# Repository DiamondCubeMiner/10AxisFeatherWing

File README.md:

# 10AxisFeatherWing #
A 10-DOF Featherwing, powered by BNO055 and BME280.

## Description ##
This featherwing uses I2C to connect both the IMU (BNO055) and the altimeter (BME280) to the Feather.
I made this to design projects that require a 10-DOF IMU in a tiny package where breakouts can affect the weight a lot and may not be a good option, such as a quadcopter, a model plane, or a model rocket.

## Drivers ##
This project is designed to use [Adafruit Unified Sensor Drivers](https://github.com/adafruit/Adafruit_Sensor).
  - [Adafruit_BNO055](https://github.com/adafruit/Adafruit_BNO055)
  - [Adafruit_BME280_Library](https://github.com/adafruit/Adafruit_BME280_Library/)

If you are experiencing problems with the Adafruit_BME280_Library, you may use Seeed Studio's [Grove_BME280](https://github.com/Seeed-Studio/Grove_BME280) drivers. It has been tested to work with the 10AxisFeatherWing.

## Thanks ##
This project is derived from the following projects:
  - [Adafruit-ADXL343-ADT7410-Featherwing-PCB](https://github.com/adafruit/Adafruit-ADXL343-ADT7410-Featherwing-PCB)
  - [Adafruit-BNO055-Breakout-PCB](https://github.com/adafruit/Adafruit-BNO055-Breakout-PCB)
  - [Adafruit-BME280-Breakout-PCB](https://github.com/adafruit/Adafruit-BME280-Breakout-PCB)

Thanks to Adafruit for their open-source schematics!

Thanks to ppelleti for the awesome FeatherWing Template!

[FeatherWing-template-KiCad](https://github.com/ppelleti/FeatherWing-template-KiCad)

## License ##
This work is licensed under the Creative Commons Attribution-ShareAlike 3.0 Unported License. To view a copy of this license, visit http://creativecommons.org/licenses/by-sa/3.0/ or by opening license.txt included in this project.

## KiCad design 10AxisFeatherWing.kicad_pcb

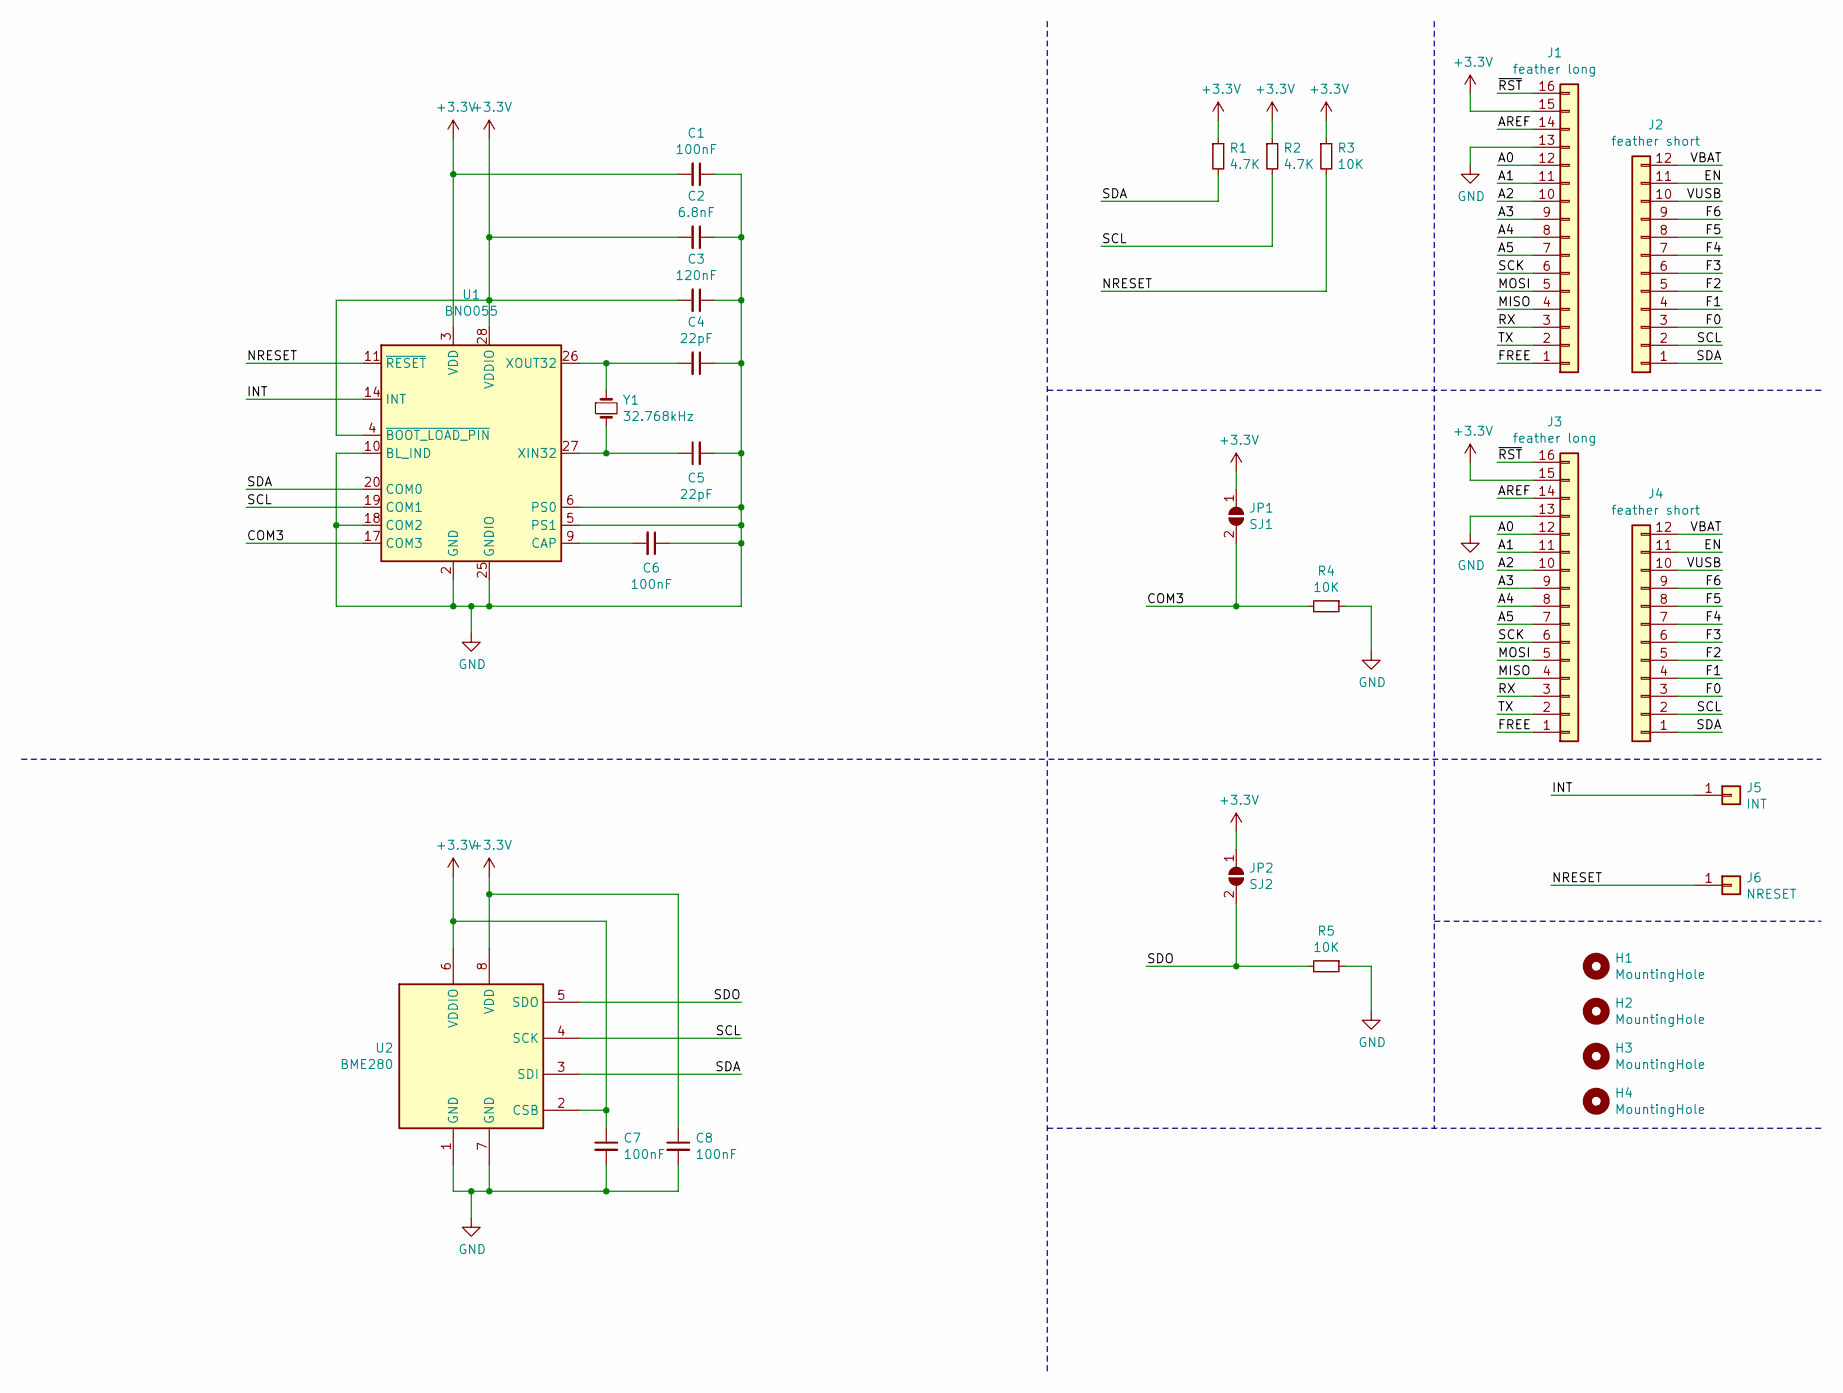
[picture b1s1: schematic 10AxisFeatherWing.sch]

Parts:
C1, C6, C7, C8: 100nF; C_0603_1608Metric
C2: 6.8nF; C_0603_1608Metric
C3: 120nF; C_0603_1608Metric
C4, C5: 22pF; C_0603_1608Metric
H1, H2, H3, H4: MountingHole; MountingHole_2.7mm_M2.5
J1: feather long; PinHeader_1x16_P2.54mm_Vertical
J2: feather short; PinHeader_1x12_P2.54mm_Vertical
J3: feather long; PinSocket_1x16_P2.54mm_Vertical
J4: feather short; PinSocket_1x12_P2.54mm_Vertical
J5: INT; SolderWirePad_1x01_Drill0.8mm
J6: NRESET; SolderWirePad_1x01_Drill0.8mm
JP1: SJ1; SolderJumper-2_P1.3mm_Open_Pad1.0x1.5mm
JP2: SJ2; SolderJumper-2_P1.3mm_Open_Pad1.0x1.5mm
R1, R2: 4.7K; R_0603_1608Metric
R3, R4, R5: 10K; R_0603_1608Metric
U1: BNO055; LGA-28_5.2x3.8mm_P0.5mm
U2: BME280; Bosch_LGA-8_2.5x2.5mm_P0.65mm_ClockwisePinNumbering
Y1: 32.768kHz; Crystal_SMD_3215-2Pin_3.2x1.5mm

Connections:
+3V3: C1.2, C2.2, C3.2, C7.1, C8.1, J1.15, J3.15, JP1.1 (A), JP2.1 (A), R1.1, R2.1, R3.1, U1.3 (VDD), U1.4 (~BOOT_LOAD_PIN), U1.28 (VDDIO), U2.2 (CSB), U2.6 (VDDIO), U2.8 (VDD)
/A0: J1.12, J3.12
/A1: J1.11, J3.11
/A2: J1.10, J3.10
/A3: J1.9, J3.9
/A4: J1.8, J3.8
/A5: J1.7, J3.7
/AREF: J1.14, J3.14
/COM3: JP1.2 (B), R4.2, U1.17 (COM3)
/EN: J2.11, J4.11
/F0: J2.3, J4.3
/F1: J2.4, J4.4
/F2: J2.5, J4.5
/F3: J2.6, J4.6
/F4: J2.7, J4.7
/F5: J2.8, J4.8
/F6: J2.9, J4.9
/FREE: J1.1, J3.1
/INT: J5.1, U1.14 (INT)
/MISO: J1.4, J3.4
/MOSI: J1.5, J3.5
/NRESET: J6.1, R3.2, U1.11 (~RESET)
/RX: J1.3, J3.3
/SCK: J1.6, J3.6
/SCL: J2.2, J4.2, R2.2, U1.19 (COM1), U2.4 (SCK)
/SDA: J2.1, J4.1, R1.2, U1.20 (COM0), U2.3 (SDI)
/SDO: JP2.2 (B), R5.2, U2.5 (SDO)
/TX: J1.2, J3.2
/VBAT: J2.12, J4.12
/VUSB: J2.10, J4.10
/~RST: J1.16, J3.16
GND: C1.1, C2.1, C3.1, C4.1, C5.2, C6.1, C7.2, C8.2, J1.13, J3.13, R4.1, R5.1, U1.2 (GND), U1.5 (PS1), U1.6 (PS0), U1.10 (BL_IND), U1.15 (GNDIO), U1.16 (GNDIO), U1.18 (COM2), U1.25 (GNDIO), U2.1 (GND), U2.7 (GND)
unnamed: C4.2, U1.26 (XOUT32), Y1.1
unnamed: C5.1, U1.27 (XIN32), Y1.2
unnamed: C6.2, U1.9 (CAP)

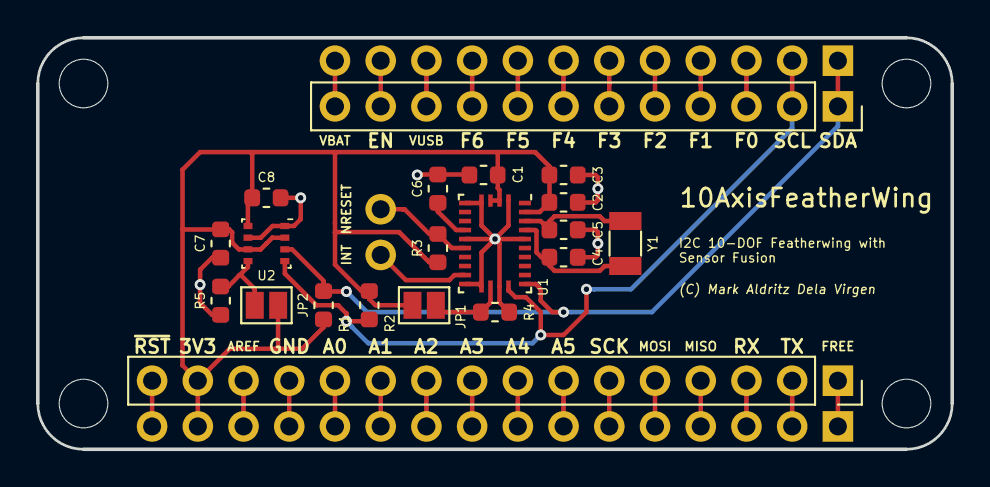
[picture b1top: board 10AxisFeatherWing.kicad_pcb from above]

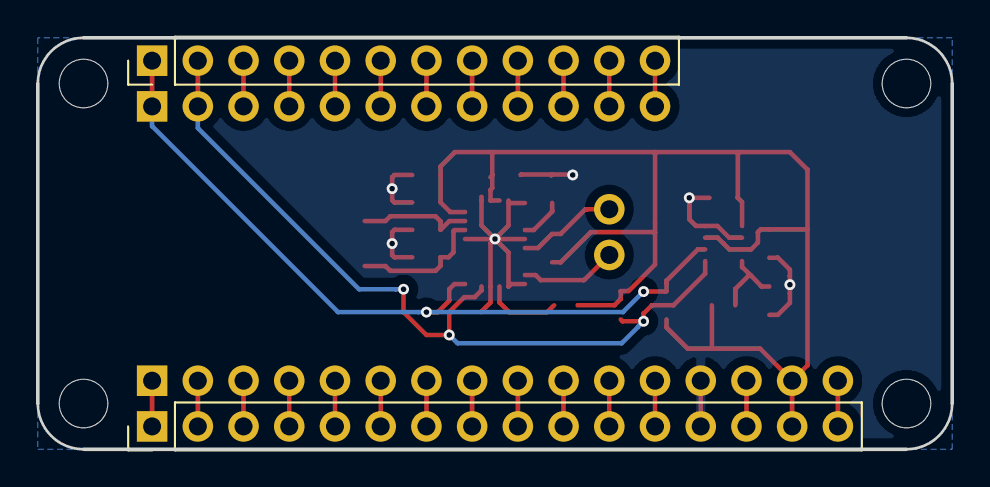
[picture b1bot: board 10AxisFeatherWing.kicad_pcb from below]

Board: 2 copper layers, 50.8 x 22.9 mm, 28 parts (2 on the bottom side), 35 nets.

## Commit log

2019-12-20 Initial upload
2019-12-20 Update README.md
    Added a line break fix on the Thanks section.
2019-12-22 Fixed IMU VDDIO not connected
2019-12-24 Added new features
    Added RESET button, INT breakout, and silk text.
2019-12-26 Corrected crystal capacitor values
2019-12-31 Migration to KiCad
2020-01-05 Updated features
    Replaced NRESET with pin instead of a button, Added silk text
2020-01-07 Minor format fix
2020-01-12 Increased trace width
2020-01-13 Updated PCB
2020-02-06 Fixed electrical connections
    Fixed the following electrical connection errors:
    > Pin 6 on BNO055 not connected to GND
    > SDA and SCL vias too close
    > Pin 18 on BNO055 GND relocated
2020-02-06 Removed STEMMA connector
    STEMMA connectors should have 3.3V to 5V level shifting and power regulation.
    This board does not have those features, so they were removed.
2020-02-06 Revert "Removed STEMMA connector"
    This reverts commit 5727fb72f54931faedf32c304c5adffcc3f247c0.
2020-02-07 Fixed C7 not connected to BME280 pin 6
    C7 is a decoupling capacitor, and should be connected to both VDD.
2020-04-09 Update README.md
    Added troubleshooting for BME280 library.
2020-09-23 EagleCAD Refactor
    - Switched to EagleCAD. Now uses microbuilder.lbr used by Adafruit Industries
    - Removed filter caps
    - Added STEMMA connector
    - Adafruit Logo! Heavily based on their latest 9-DoF Combo featherwings (Should I remove it?)
2020-11-12 Revert "EagleCAD Refactor"
    This reverts commit e0a2de9822f84c03f4477eba47b3f3700a9858d7.
2020-11-16 I2C pull-up resistor fix
    Changed I2C pull-up resistor values from 10K to 4.7K
